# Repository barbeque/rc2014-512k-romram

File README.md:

## The Board

## Licensing and Credits
This board is based on [the schematic listed on the RC2014 website](https://rc2014.co.uk/modules/512k-rom-512k-ram-module/), which is in turn derived from [Sergey Kiselev's Zeta 2 SBC](https://github.com/skiselev/zeta_sbc) (GPLv3). Please honour the licensing for any derivatives made of this board.

Symbol for the AS6C4008 ROM comes from SnapEDA.

## Version 2
Fixed:
 - D0 was not written into the 7474
 - A18 was not connected on the RAM, due to a buggy (copy-paste error) SnapEDA symbol.

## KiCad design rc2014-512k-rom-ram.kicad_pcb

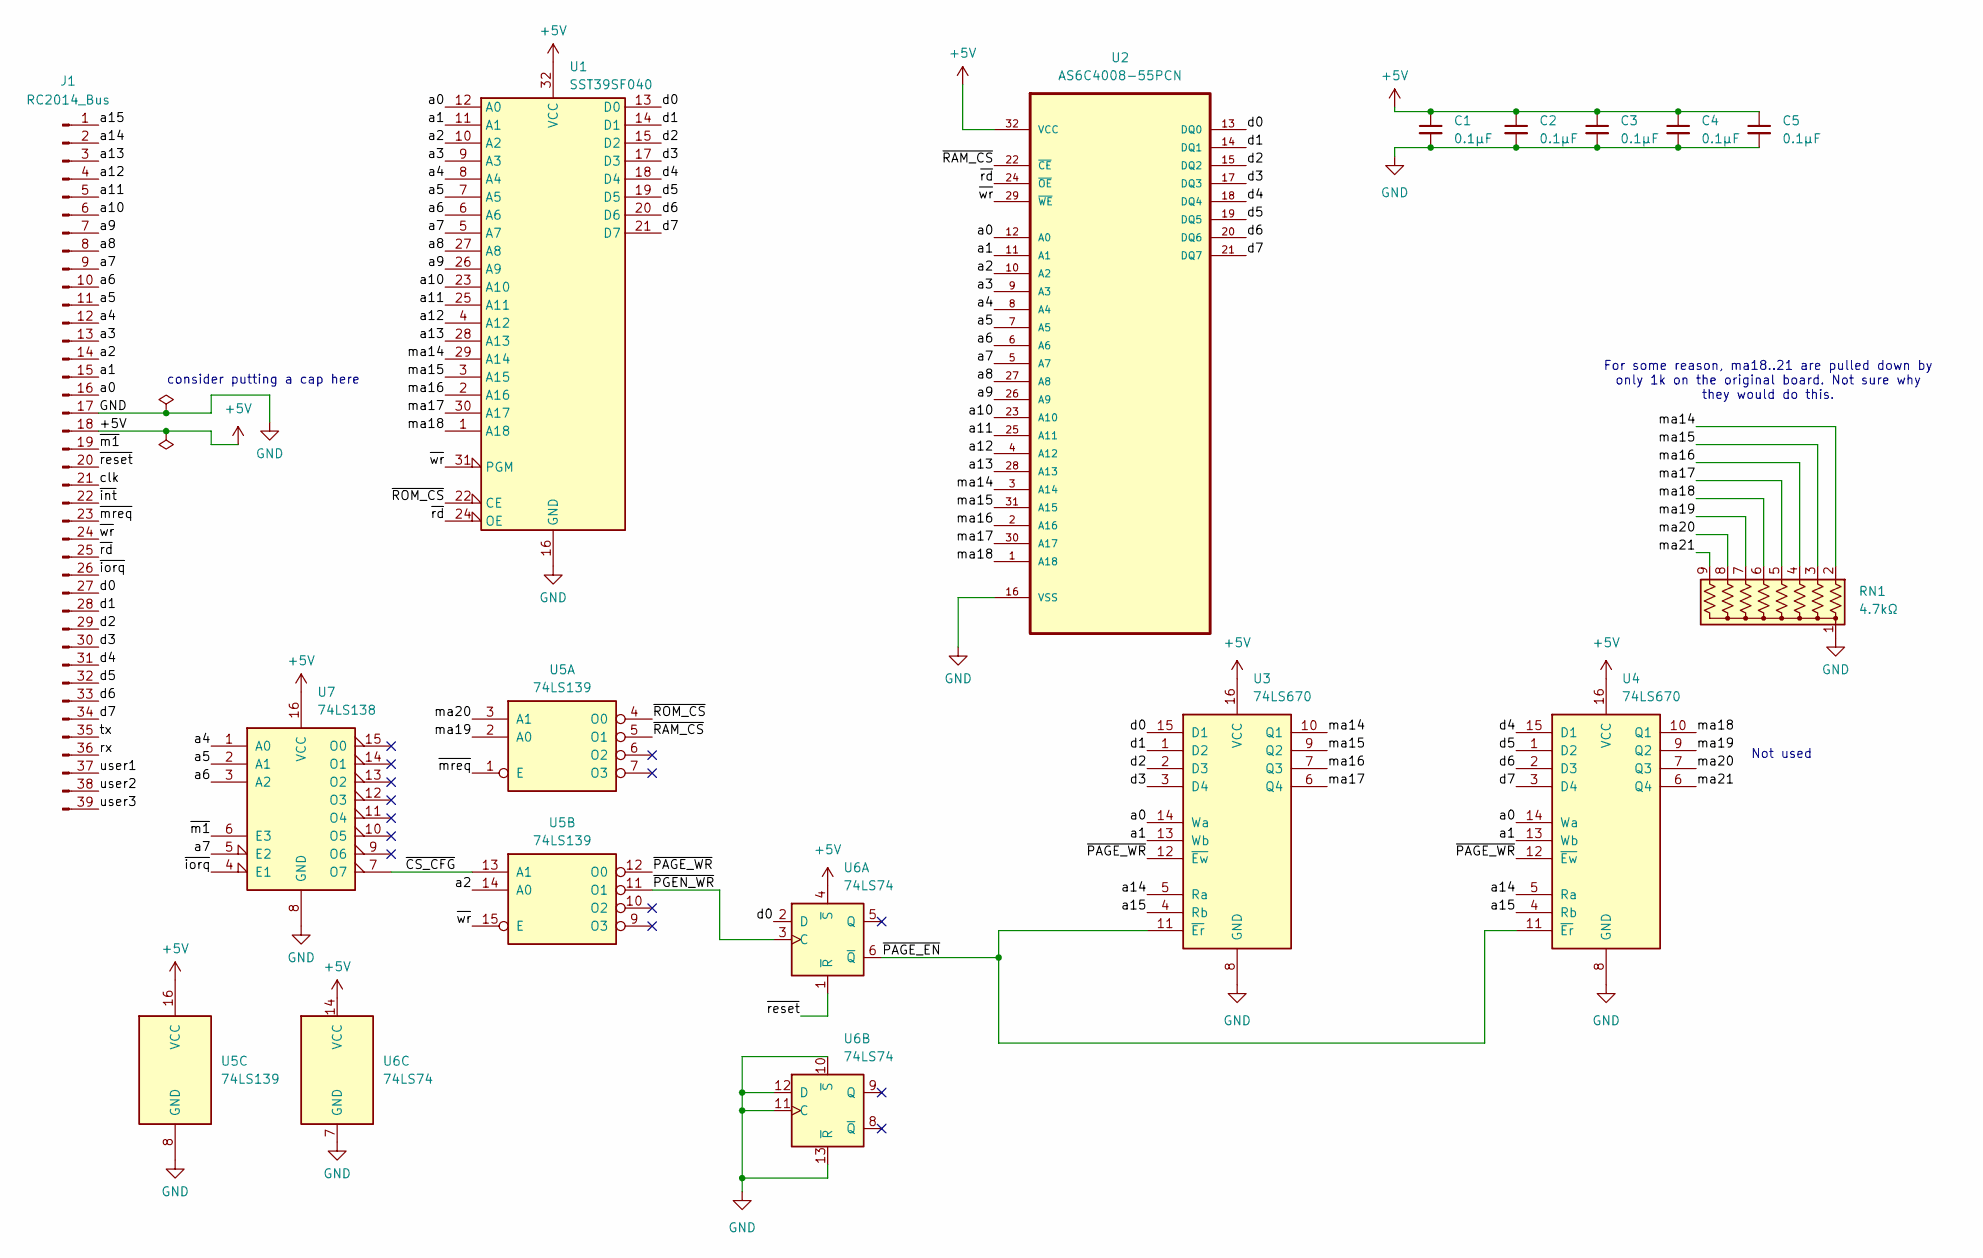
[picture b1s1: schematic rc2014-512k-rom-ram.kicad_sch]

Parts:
C1, C2, C3, C4, C5: 0.1µF; C_Disc_D4.7mm_W2.5mm_P5.00mm
J1: RC2014_Bus; PinHeader_1x39_P2.54mm_Vertical
RN1: 4.7kΩ; R_Array_SIP9
U1: SST39SF040; DIP-32_W15.24mm_Socket_LongPads
U2: AS6C4008-55PCN; DIP254P1524X393-32; MPN AS6C4008-55PCN
U3, U4: 74LS670; DIP-16_W7.62mm_Socket_LongPads
U5: 74LS139; DIP-16_W7.62mm_Socket_LongPads
U6: 74LS74; DIP-14_W7.62mm_Socket_LongPads
U7: 74LS138; DIP-16_W7.62mm_Socket_LongPads

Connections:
+5V: C1.1, C2.1, C3.1, C4.1, C5.1, J1.18, U1.32 (VCC), U2.32 (VCC), U3.16 (VCC), U4.16 (VCC), U5.16 (VCC), U6.4 (~S), U6.14 (VCC), U7.16 (VCC)
/a0: J1.16, U1.12 (A0), U2.12 (A0), U3.14 (Wa), U4.14 (Wa)
/a1: J1.15, U1.11 (A1), U2.11 (A1), U3.13 (Wb), U4.13 (Wb)
/a2: J1.14, U1.10 (A2), U2.10 (A2), U5.14 (A0)
/a3: J1.13, U1.9 (A3), U2.9 (A3)
/a4: J1.12, U1.8 (A4), U2.8 (A4), U7.1 (A0)
/a5: J1.11, U1.7 (A5), U2.7 (A5), U7.2 (A1)
/a6: J1.10, U1.6 (A6), U2.6 (A6), U7.3 (A2)
/a7: J1.9, U1.5 (A7), U2.5 (A7), U7.5 (E2)
/a8: J1.8, U1.27 (A8), U2.27 (A8)
/a9: J1.7, U1.26 (A9), U2.26 (A9)
/a10: J1.6, U1.23 (A10), U2.23 (A10)
/a11: J1.5, U1.25 (A11), U2.25 (A11)
/a12: J1.4, U1.4 (A12), U2.4 (A12)
/a13: J1.3, U1.28 (A13), U2.28 (A13)
/a14: J1.2, U3.5 (Ra), U4.5 (Ra)
/a15: J1.1, U3.4 (Rb), U4.4 (Rb)
/clk: J1.21
/d0: J1.27, U1.13 (D0), U2.13 (DQ0), U3.15 (D1), U6.2 (D)
/d1: J1.28, U1.14 (D1), U2.14 (DQ1), U3.1 (D2)
/d2: J1.29, U1.15 (D2), U2.15 (DQ2), U3.2 (D3)
/d3: J1.30, U1.17 (D3), U2.17 (DQ3), U3.3 (D4)
/d4: J1.31, U1.18 (D4), U2.18 (DQ4), U4.15 (D1)
/d5: J1.32, U1.19 (D5), U2.19 (DQ5), U4.1 (D2)
/d6: J1.33, U1.20 (D6), U2.20 (DQ6), U4.2 (D3)
/d7: J1.34, U1.21 (D7), U2.21 (DQ7), U4.3 (D4)
/ma14: RN1.2 (R1), U1.29 (A14), U2.3 (A14), U3.10 (Q1)
/ma15: RN1.3 (R2), U1.3 (A15), U2.31 (A15), U3.9 (Q2)
/ma16: RN1.4 (R3), U1.2 (A16), U2.2 (A16), U3.7 (Q3)
/ma17: RN1.5 (R4), U1.30 (A17), U2.30 (A17), U3.6 (Q4)
/ma18: RN1.6 (R5), U1.1 (A18), U2.1 (A18), U4.10 (Q1)
/ma19: RN1.7 (R6), U4.9 (Q2), U5.2 (A0)
/ma20: RN1.8 (R7), U4.7 (Q3), U5.3 (A1)
/ma21: RN1.9 (R8), U4.6 (Q4)
/rx: J1.36
/tx: J1.35
/user1: J1.37
/user2: J1.38
/user3: J1.39
/~CS_CFG: U5.13 (A1), U7.7 (O7)
/~PAGE_EN: U3.11 (~Er), U4.11 (~Er), U6.6 (~Q)
/~PAGE_WR: U3.12 (~Ew), U4.12 (~Ew), U5.12 (O0)
/~PGEN_WR: U5.11 (O1), U6.3 (C)
/~RAM_CS: U2.22 (CE), U5.5 (O1)
/~ROM_CS: U1.22 (CE), U5.4 (O0)
/~int: J1.22
/~iorq: J1.26, U7.4 (E1)
/~m1: J1.19, U7.6 (E3)
/~mreq: J1.23, U5.1 (E)
/~rd: J1.25, U1.24 (OE), U2.24 (OE)
/~reset: J1.20, U6.1 (~R)
/~wr: J1.24, U1.31 (PGM), U2.29 (WE), U5.15 (E)
GND: C1.2, C2.2, C3.2, C4.2, C5.2, J1.17, RN1.1 (common), U1.16 (GND), U2.16 (VSS), U3.8 (GND), U4.8 (GND), U5.8 (GND), U6.7 (GND), U6.10 (~S), U6.11 (C), U6.12 (D), U6.13 (~R), U7.8 (GND)

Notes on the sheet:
Not used
For some reason, ma18..21 are pulled down by only 1k on the original board. Not sure why they would do this.
consider putting a cap here

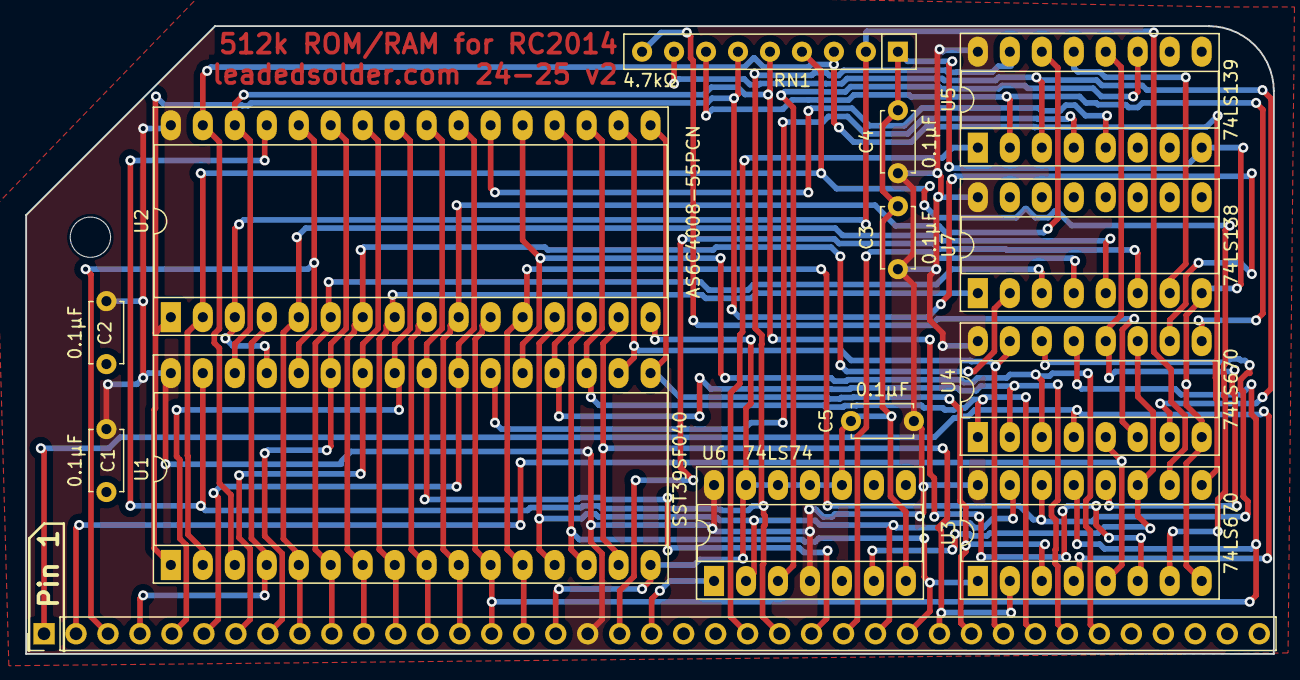
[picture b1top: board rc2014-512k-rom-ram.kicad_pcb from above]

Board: 2 copper layers, 99.1 x 49.9 mm, 14 parts (0 on the bottom side), 46 nets.

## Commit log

2024-06-25 Redrawn schematic
2024-06-25 Oops
2024-06-25 Finally fully routed
2024-06-25 labels
2024-06-25 Send v1 to fab
2024-06-25 Send to JLCPCB
2024-06-25 Images
2024-06-25 OSHW logo
2024-06-25 Create LICENSE
2024-06-25 Credits
2024-06-25 SnapEDA
2025-01-18 Fix missing d0 line
2025-01-18 A18 shouldn't be broken on 4008
2025-01-19 Fix root symbol
2025-01-19 Remove useless backup file
2025-01-20 Fix power flag complaint
2025-01-20 Schematic cleanup
2025-02-22 Solid fill
2025-02-22 KiCad 9; fix designators
2026-06-20 Comments on memory map
2026-06-20 Big gate oops
